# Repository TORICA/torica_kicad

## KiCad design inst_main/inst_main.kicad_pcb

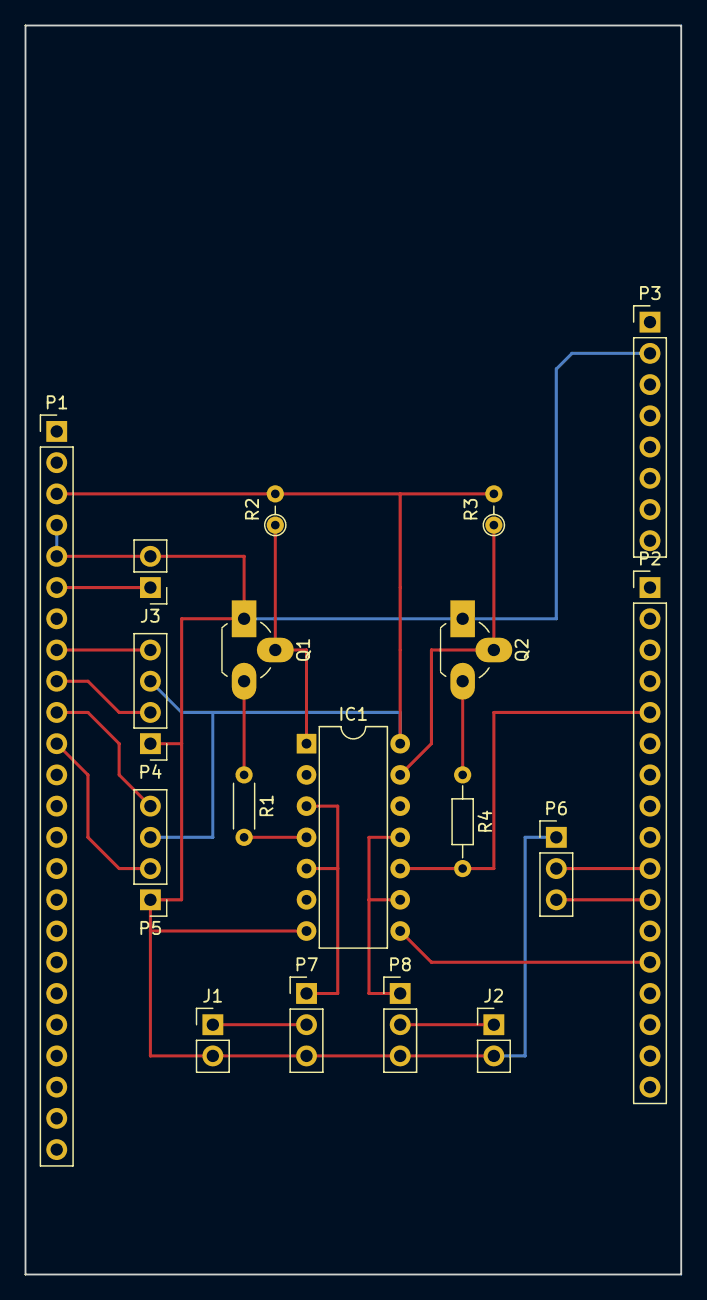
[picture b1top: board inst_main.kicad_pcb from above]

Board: 2 copper layers, 53.3 x 101.6 mm, 18 parts (0 on the bottom side), 23 nets.

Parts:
IC1: SN74HC125N; DIP-14_W7.62mm
J1, J2, J3: B2B-XH-A(LF)(SN); Pin_Header_Straight_1x02_Pitch2.54mm
P1: ANALOG; Pin_Header_Straight_1x24_Pitch2.54mm
P2: DIGITAL_L; Pin_Header_Straight_1x17_Pitch2.54mm
P3: DIGITAL_H; Pin_Header_Straight_1x08_Pitch2.54mm
P4: JS_H; Pin_Header_Straight_1x04_Pitch2.54mm
P5: JS_V; Pin_Header_Straight_1x04_Pitch2.54mm
P6: SDC; Pin_Header_Straight_1x03_Pitch2.54mm
P7: SVH; Pin_Header_Straight_1x03_Pitch2.54mm
P8: SVV; Pin_Header_Straight_1x03_Pitch2.54mm
Q1, Q2: Q_NPN_ECB; TO-92_Rugged
R1: R; R_Axial_DIN0204_L3.6mm_D1.6mm_P5.08mm_Horizontal
R2, R3: R; R_Axial_DIN0204_L3.6mm_D1.6mm_P2.54mm_Vertical
R4: R; R_Axial_DIN0204_L3.6mm_D1.6mm_P7.62mm_Horizontal

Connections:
5V: IC1.14, P1.3, P4.3, P5.3, R2.2, R3.2
A0: P1.8, P4.4
A1: P1.9, P4.2
A2: P1.10, P5.4
A3: P1.11, P5.2
CTRLGND: IC1.7, J1.2, J2.2, J3.2, P1.4, P1.5, P3.2, P4.1, P5.1, P6.1, P7.3, P8.3, Q1.1, Q2.1
D2: IC1.4, P2.6, R1.2
D3: IC1.10, P2.5, R4.2
unnamed: IC1.1, Q1.2, R2.1
unnamed: IC1.3, IC1.5, P7.1
unnamed: IC1.9, IC1.11, P8.1
unnamed: IC1.13, Q2.2, R3.1
unnamed: Q1.3, R1.1
unnamed: Q2.3, R4.1
RX1: IC1.6, P2.15
RX2: IC1.8, P2.13
RX3: P2.11, P6.3
SVH11V1: J1.1, P7.2
SVV11V1: J2.1, P8.2
TX1: IC1.2, P2.14
TX2: IC1.12, P2.12
TX3: P2.10, P6.2
Vin: J3.1, P1.6

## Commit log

2017-05-02 操舵系主基板の設計
2017-05-02 PLCC44pパッケージのブレイクアウトボード
2017-05-02 測定系との通信コネクタを4p->3pに変更（5Vを削除）
2017-05-02 CTRL7V4->Vin Rev2.1
2017-05-02 フットプリントの配置と配線
2017-05-02 P6のRXとTX入れ替え。フットプリントの配置と配線完了
2017-05-02 フットプリントに図名等入れた
2017-05-12 update schs
2017-05-13 mod ctrl_main wiring
2017-06-19 add inst_main
2017-06-19 mod pitch_sensor
2017-06-19 mod ctrl_main
2017-06-20 mod inst_main rev0.1
2017-06-27 mod inst_main sch and pcb (Rev. 0.2)
